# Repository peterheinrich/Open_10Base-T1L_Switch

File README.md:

# !!! UNTESTED DESIGN STUDY - WORK IN PROGRESS !!!

# Open_10Base-T1L_Switch
Open Hardware 7-Port 10Base-T1L and 1-Port 20/100/1000Base-T Field Switch Design

Schematic: [Open_10Base-T1L_Switch-sch.pdf](Open_10Base-T1L_Switch-sch.pdf)

## Architecture ##
Two 5-port switch ICs (SJA1105Q) form the basis of the design. Daisy chaining the two ICs gives a total of 8 ports.
Seven of these ports are attachted to 10Base-T1L PHYs (ADIN1100), while one port is attached to a 1000Base-T PHY (KSZ9131) as uplink. 

Each of the 10Base-T1L ports offer power over datalines utilizing two 5-Port power management controllers (LTC4296) with SCC support for power delivery negotiation. The design is 24V only and supports PoDL Class 12.

An RP2040 functions as a system controller configuring the switch components.

## Current Placement ##

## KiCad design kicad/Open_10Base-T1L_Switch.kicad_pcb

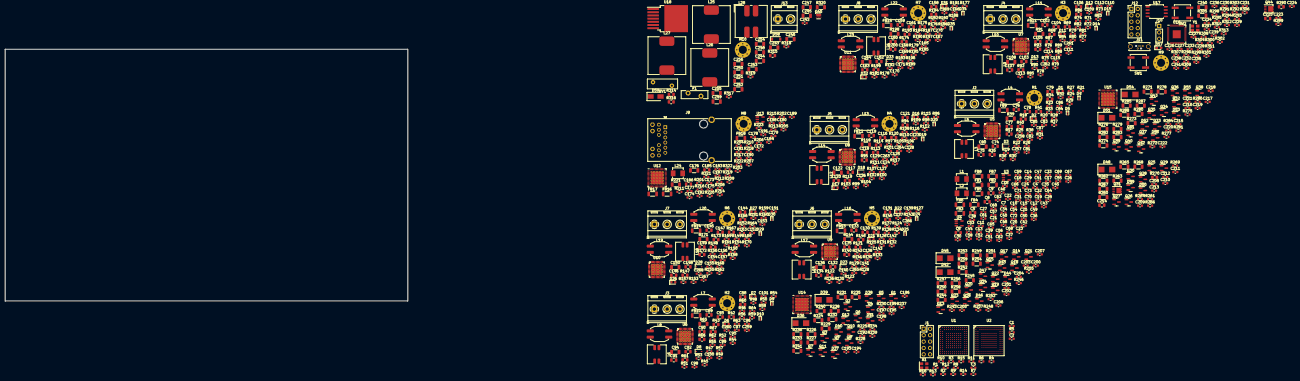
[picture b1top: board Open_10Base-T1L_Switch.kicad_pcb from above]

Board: 8 copper layers, 160.0 x 100.0 mm, 789 parts (0 on the bottom side), 588 nets, no tracks yet.

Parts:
C1, C10, C11, C12, C13, C14, C15, C16, C17, C18, C19, C20, C21, C22, C23, C24, C25, C26, C27, C29, C30, C31, C32, C33, C34, C35, C36, C37, C38, C39, C41, C42, C43, C44, C45, C46, C47, C48, C49, C50, C51, C53, C54, C55, C56, C57, C58, C59, C60, C61, C62, C63, C65, C66, C67, C68, C69, C70, C71, C72, C73, C83, C84, C85, C86, C87, C97, C98, C99, C100, C101, C111, C112, C113, C114, C115, C125, C126, C127, C128, C129, C139, C140, C141, C142, C143, C153, C154, C155, C156, C157, C167, C168, C169, C170, C171, C172, C173, C174, C175, C177, C178, C179, C180, C181, C182, C183, C184, C187, C188, C189, C190, C191, C193, C197, C201, C205, C209, C216, C220, C227, C228, C229, C230, C231, C232, C233, C234, C235, C237, C239: 100n; C_0603_1608Metric
C2, C3: 100p; C_0603_1608Metric
C4, C7, C28, C40, C52, C64, C82, C96, C110, C124, C138, C152, C166, C226, C236: 1u; C_0603_1608Metric
C5, C6, C8, C9, C185, C186: 10u; C_0805_2012Metric
C74, C75, C76, C77, C88, C89, C90, C91, C102, C103, C104, C105, C116, C117, C118, C119, C130, C131, C132, C133, C144, C145, C146, C147, C158, C159, C160, C161: 220n; C_0805_2012Metric
C78, C79, C92, C93, C106, C107, C120, C121, C134, C135, C148, C149, C162, C163: 10n; C_0805_2012Metric
C80, C94, C108, C122, C136, C150, C164, C176, C240, C256: 1u; C_1206_3216Metric
C81, C95, C109, C123, C137, C151, C165: 680n; C_0603_1608Metric
C192, C196, C200, C204, C208, C215, C219: 2u2; C_0603_1608Metric
C194, C195, C198, C199, C202, C203, C206, C207, C210, C211, C217, C218, C221, C222: 2n2; C_0603_1608Metric
C212, C213, C223, C224: 1n; C_0603_1608Metric
C214, C225: 2u2; C_0805_2012Metric
C238, C241, C258, C260, C262, C264, C266, C268, C270: 10p; C_0603_1608Metric
C242: 10n; C_0603_1608Metric
C243, C244, C245, C246, C247, C251, C252, C253, C254, C255: 22u; C_1206_3216Metric
C248, C249, C250: 47u; C_1206_3216Metric
C257, C259, C261, C263, C265, C267, C269: 8p2; C_0603_1608Metric
D1, D2, D6, D7, D11, D12, D16, D17, D21, D22, D26, D27, D31, D32: LED; LED_0603_1608Metric
D3, D8, D13, D18, D23, D28, D33: CDSOD323-T36SC; D_SOD-323
D4, D5, D9, D10, D14, D15, D19, D20, D24, D25, D29, D30, D34, D35: UCLAMP3311P; SLP1006P2
D36, D39, D42, D45, D48, D51, D54: S1B-13-F; D_SMB
D37, D40, D43, D46, D49, D52, D55: BAT54; SOT-23-DIODE
D38, D41, D44, D47, D50, D53, D56: MMBD914LT1G; SOT-23-DIODE
D57: LED; LED_0603_1608Metric_Pad1.05x0.95mm_HandSolder
D58: BZT52C10; D_SOD-123
D59: SDT5A60SA-13; D_SMA
F1: RUEF500; Fuse_Bourns_MF-RG500
FB1, FB2, FB3, FB4, FB5, FB6, FB7, FB8, FB16, FB17, FB18: 782763301; L_1206_3216Metric
FB9, FB10, FB11, FB12, FB13, FB14, FB15: FerriteBead; L_1206_3216Metric
H1, H2, H3, H4, H5, H6, H7, H8, H9, H10: CHASSIS_PE; MountingHole_3.2mm_M3_Pad_Via
J1, J12: Conn_ARM_JTAG_SWD_10; PinHeader_2x05_P2.54mm_Vertical
J2: PHY0_MDI; TerminalBlock_RND_205-00288_1x03_P5.08mm_Horizontal
J3: PHY1_MDI; TerminalBlock_RND_205-00288_1x03_P5.08mm_Horizontal
J4: PHY2_MDI; TerminalBlock_RND_205-00288_1x03_P5.08mm_Horizontal
J5: PHY3_MDI; TerminalBlock_RND_205-00288_1x03_P5.08mm_Horizontal
J6: PHY4_MDI; TerminalBlock_RND_205-00288_1x03_P5.08mm_Horizontal
J7: PHY5_MDI; TerminalBlock_RND_205-00288_1x03_P5.08mm_Horizontal
J8: PHY6_MDI; TerminalBlock_RND_205-00288_1x03_P5.08mm_Horizontal
J9: JK0654219; RJ45_Pulse_JK0654219NL_Horizontal
J10: CONSOLE; PinHeader_1x03_P2.54mm_Vertical
J11: USB_B_Micro; USB_Micro-B_Wuerth_614105150721_Vertical_CircularHoles
J13: PWR IN; TerminalBlock_RND_205-00287_1x02_P5.08mm_Horizontal
L1, L2, L24: IHLP1616BZER2R2M1A; L_Vishay_IHLP-1616
L3, L6, L9, L12, L15, L18, L21: PID75-251M
L4, L7, L10, L13, L16, L19, L22: ICI70CGI-222; ICI70CGI
L5, L8, L11, L14, L17, L20, L23: RCM70CGI-471; ICI70CGI
L25, L26, L27: MSS1583-103MED; MSS1583
L28: B82477D6103M603; L_Bourns_SRF1260
Q1, Q4, Q5, Q7, Q10, Q11, Q13, Q16, Q17, Q19, Q22, Q23, Q25, Q28, Q29, Q32, Q35, Q36, Q38, Q41, Q42: DMG3414U; SOT-23
Q2, Q8, Q14, Q20, Q26, Q33, Q39: MMBTA06; SOT-23
Q3, Q6, Q9, Q12, Q15, Q18, Q21, Q24, Q27, Q30, Q34, Q37, Q40, Q43: MMBT3904; SOT-23
Q31, Q44: SiS412DN; Vishay_PowerPAK_1212-8_Single
Q45: SiA449DJ; Vishay_PowerPAK_SC70-6L_Single
R1, R2, R3, R4, R5, R6, R7, R8, R9, R10, R11, R14, R24, R25, R27, R28, R31, R33, R36, R37, R38, R50, R51, R53, R54, R57, R59, R62, R63, R64, R76, R77, R79, R80, R83, R85, R88, R89, R90, R103, R104, R106, R107, R110, R112, R115, R116, R117, R129, R130, R132, R133, R136, R138, R141, R142, R143, R156, R157, R159, R160, R163, R165, R168, R169, R170, R183, R184, R186, R187, R190, R192, R195, R196, R197, R207, R208, R209, R210, R211, R212, R213, R214, R215, R216, R217, R218: 22; R_0603_1608Metric
R12, R15, R99, R100, R308: 1K; R_0603_1608Metric
R13, R16: 560; R_0603_1608Metric
R17, R34, R42, R60, R68, R86, R94, R113, R121, R139, R147, R166, R174, R193: 0; R_0805_2012Metric
R18, R35, R43, R61, R69, R87, R95, R114, R122, R140, R148, R167, R175, R194: 100K; R_0805_2012Metric
R19, R20, R44, R45, R70, R71, R96, R97, R123, R124, R149, R150, R176, R177, R313, R321, R322: 470; R_0603_1608Metric
R21, R46, R47, R72, R73, R125, R126, R151, R152, R153, R178, R179, R180, R317: 4K7; R_0603_1608Metric
R22, R32, R48, R58, R74, R84, R101, R111, R127, R137, R154, R164, R181, R191: 10K2; R_0603_1608Metric
R23, R30, R49, R56, R75, R82, R102, R109, R128, R135, R155, R162, R182, R189: 49.9; R_0603_1608Metric
R26, R29, R52, R55, R78, R81, R105, R108, R131, R134, R158, R161, R185, R188: 5K1; R_0603_1608Metric
R39, R65, R91, R118, R144, R171, R198, R221, R305, R320: 4M7; R_1206_3216Metric
R40, R41, R66, R67, R92, R93, R119, R120, R145, R146, R172, R173, R199, R200: 100; R_0805_2012Metric
R98, R201, R202, R203, R204, R205, R206, R219, R220, R230, R239, R248, R257, R266, R277, R286, R291, R319: 10K; R_0603_1608Metric
R222, R223, R312: 3K3; R_0603_1608Metric
R224, R233, R242, R251, R260, R271, R280: 0R24; R_1206_3216Metric
R225, R234, R243, R252, R261, R272, R281: 50K; R_0603_1608Metric
R226, R235, R244, R253, R262, R273, R282: 20; R_1206_3216Metric
R227, R236, R245, R254, R263, R274, R283: 50; R_1206_3216Metric
R228, R237, R246, R255, R264, R275, R284: 5K; R_0603_1608Metric
R229, R231, R238, R240, R247, R249, R256, R258, R265, R267, R276, R278, R285, R287: 5; R_1206_3216Metric
R232, R241, R250, R259, R268, R279, R288: 0R062; R_1206_3216Metric
R269, R289: 24K3; R_0603_1608Metric
R270, R290: 49K9; R_0805_2012Metric
R292, R296: 27; R_0603_1608Metric
R293, R294, R295, R297, R298, R299, R300, R301, R302, R303, R304, R306, R307, R309, R310, R311: 330; R_0603_1608Metric
R314, R315, R316: 1R0; R_0805_2012Metric
R318: 3K; R_0603_1608Metric
RV1: MOV-10D390K; RV_Disc_D12mm_W3.9mm_P7.5mm
SW1, SW2: USB_PGM; SW_Push_1P1T_NO_CK_KSC6xxJ
U1, U2: SJA1105Q; LFBGA_12x12mm_P0.8mm
U3, U4, U13: SC4626C; SOT-23-5
U5, U6, U7, U8, U9, U10, U11: ADIN1100; LFCSP-40_EP_TheramVias
U12: KSZ9131RNX; VQFN-48-1EP_7x7mm_P0.5mm_EP5.15x5.15mm_ThermalVias
U14, U15: LTC4296-1; QFN-48-1EP_7x7mm_P0.5mm_EP5.3x5.3mm_ThermalVias
U16: RP2040; QFN-56-1EP_7x7mm_P0.4mm_EP3.2x3.2mm
U17: IS25LP128F-JBLE; SOIC-8_5.23x5.23mm_P1.27mm
U18: LM22678TJ-ADJ; TO-263-7_TabPin8
X1: ASE-25.000MHz; Oscillator_SMD_Abracon_ASE-4Pin_3.2x2.5mm
Y1: 12MHz; Crystal_SMD_Abracon_ABM8G-4Pin_3.2x2.5mm

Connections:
25MHz_REFCLK: R14.1, U12.46 (XI)
+3V3: C1.1, C4.1, C7.1, C87.1, C101.1, C115.1, C129.1, C143.1, C157.1, C171.1, C185.1, C187.1, C188.1, C189.1, C229.1, C230.1, C231.1, C232.1, C233.1, C234.1, C235.1, C236.1, C239.1, D1.2 (A), D2.2 (A), D6.2 (A), D7.2 (A), D11.2 (A), D12.2 (A), D16.2 (A), D17.2 (A), D21.2 (A), D22.2 (A), D26.2 (A), D27.2 (A), D31.2 (A), D32.2 (A), D37.1 (K), D40.1 (K), D43.1 (K), D46.1 (K), D49.1 (K), D52.1 (K), D55.1 (K), FB1.1, FB2.1, FB3.2, FB4.2, FB9.2, FB10.2, FB11.2, FB12.2, FB13.2, FB14.2, FB15.2, FB18.2, J1.1 (VTref), J9.14 (LED2+), J9.16 (LED1+), J12.1 (VTref), L25.2, R21.2, R46.2, R47.2, R72.2, R73.2, R98.2, R99.2, R100.2, R125.2, R126.2, R151.2, R152.2, R153.2, R178.2, R179.2, R180.2, R201.1, R202.1, R203.1, R204.1, R205.1, R206.1, R222.1, R223.1, R225.2, R234.2, R243.2, R252.2, R261.2, R272.2, R281.2, R291.1, R314.1, R315.1, R316.1, R317.1, U5.35 (VDDIO), U6.35 (VDDIO), U7.35 (VDDIO), U8.35 (VDDIO), U9.35 (VDDIO), U10.35 (VDDIO), U11.35 (VDDIO), U12.16 (DVDDH), U12.34 (DVDDH), U12.40 (DVDDH), U13.1 (VIN), U16.1 (IOVDD), U16.10 (IOVDD), U16.22 (IOVDD), U16.33 (IOVDD), U16.42 (IOVDD), U16.43 (ADC_AVDD), U16.44 (VREG_IN), U16.48 (USB_VDD), U16.49 (IOVDD), U17.8 (VCC), X1.1 (EN), X1.4 (Vdd)
+24V: C212.1, C223.1, C243.1, D58.1 (K), L27.1, Q45.4 (S), R224.1, R233.1, R242.1, R251.1, R260.1, R271.1, R280.1, U14.4 (HSNSP0), U14.6 (IN), U14.36 (HSNSP4), U14.40 (HSNSP3), U14.44 (HSNSP2), U14.48 (HSNSP1), U15.4 (HSNSP0), U15.6 (IN), U15.48 (HSNSP1)
/100Base-TX-PHY7/1V2: C180.1, C181.1, C182.1, C183.1, C184.1, C186.1, FB16.2, FB17.2, L24.1, U12.18 (DVDDL), U12.23 (DVDDL), U12.26 (DVDDL), U12.30 (DVDDL), U12.39 (DVDDL), U13.4 (VOUT)
/SJA1105Q Power/1V2_A: C6.1, C10.1, C11.1, C12.1, C13.1, C14.1, C15.1, C16.1, C17.1, C26.1, C50.1, FB5.1, FB7.1, L1.1, U1.D6 (VDD_CORE), U1.D9 (VDD_CORE), U1.F4 (VDD_CORE), U1.F11 (VDD_CORE), U1.J4 (VDD_CORE), U1.J11 (VDD_CORE), U1.L6 (VDD_CORE), U1.L9 (VDD_CORE), U3.4 (VOUT)
/SJA1105Q Power/1V2_B: C9.1, C18.1, C19.1, C20.1, C21.1, C22.1, C23.1, C24.1, C25.1, C38.1, C62.1, FB6.1, FB8.1, L2.1, U2.D6 (VDD_CORE), U2.D9 (VDD_CORE), U2.F4 (VDD_CORE), U2.F11 (VDD_CORE), U2.J4 (VDD_CORE), U2.J11 (VDD_CORE), U2.L6 (VDD_CORE), U2.L9 (VDD_CORE), U4.4 (VOUT)
/System Controller/CON_USB+: J11.3 (D+), R292.1
/System Controller/CON_USB-: J11.2 (D-), R296.1
/System Controller/RP_USB+: R292.2, U16.47 (USB_DP)
/System Controller/RP_USB-: R296.2, U16.46 (USB_DM)
/System Controller/SCLK: U16.52 (QSPI_SCLK), U17.6 (CLK)
/System Controller/SD0: U16.53 (QSPI_SD0), U17.5 (DI(IO0))
/System Controller/SD1: U16.55 (QSPI_SD1), U17.2 (DO(IO1))
/System Controller/SD2: U16.54 (QSPI_SD2), U17.3 (IO2)
/System Controller/SD3: U16.51 (QSPI_SD3), U17.7 (IO3)
/System Controller/SS: R312.1, U16.56 (QSPI_SS), U17.1 (~CS)
/System Controller/UART0_RXD: J10.2, U16.3 (GPIO1)
/System Controller/UART0_TXD: J10.1, U16.2 (GPIO0)
/System Controller/nRST: C237.1, J12.10 (~RESET), R291.2, SW1.2, U16.26 (RUN)
GLOBAL_RESET: R300.2, U1.P3 (RST_N), U2.P3 (RST_N), U5.5 (RESET_N), U6.5 (RESET_N), U7.5 (RESET_N), U8.5 (RESET_N), U9.5 (RESET_N), U10.5 (RESET_N), U11.5 (RESET_N), U12.42 (RESET_N)
GND: C1.2, C4.2, C5.2, C6.2, C7.2, C8.2, C9.2, C10.2, C11.2, C12.2, C13.2, C14.2, C15.2, C16.2, C17.2, C18.2, C19.2, C20.2, C21.2, C22.2, C23.2, C24.2, C25.2, C26.2, C27.2, C28.2, C29.2, C30.2, C31.2, C32.2, C33.2, C34.2, C35.2, C36.2, C37.2, C38.2, C39.2, C40.2, C41.2, C42.2, C43.2, C44.2, C45.2, C46.2, C47.2, C48.2, C49.2, C50.2, C51.2, C52.2, C53.2, C54.2, C55.2, C56.2, C57.2, C58.2, C59.2, C60.2, C61.2, C62.2, C63.2, C64.2, C65.2, C66.2, C67.2, C68.2, C69.2, C70.2, C71.2, C72.2, C73.2, C80.2, C81.2, C82.2, C83.2, C84.2, C85.2, C86.2, C87.2, C94.2, C95.2, C96.2, C97.2, C98.2, C99.2, C100.2, C101.2, C108.2, C109.2, C110.2, C111.2, C112.2, C113.2, C114.2, C115.2, C122.2, C123.2, C124.2, C125.2, C126.2, C127.2, C128.2, C129.2, C136.2, C137.2, C138.2, C139.2, C140.2, C141.2, C142.2, C143.2, C150.2, C151.2, C152.2, C153.2, C154.2, C155.2, C156.2, C157.2, C164.2, C165.2, C166.2, C167.2, C168.2, C169.2, C170.2, C171.2, C172.1, C173.1, C174.1, C175.1, C176.2, C177.2, C178.2, C179.2, C180.2, C181.2, C182.2, C183.2, C184.2, C185.2, C186.2, C187.2, C188.2, C189.2, C190.2, C191.2, C213.1, C214.1, C224.1, C225.1, C226.2, C227.2, C228.2, C229.2, C230.2, C231.2, C232.2, C233.2, C234.2, C235.2, C236.2, C237.2, C238.2, C239.2, C240.2, C241.2, C248.2, C249.2, C250.2, C251.2, C252.2, C254.2, C255.2, C256.2, C258.2, C260.2, C262.2, C264.2, C266.2, C268.2, C270.2, D4.1 (A1), D5.1 (A1), D9.1 (A1), D10.1 (A1), D14.1 (A1), D15.1 (A1), D19.1 (A1), D20.1 (A1), D24.1 (A1), D25.1 (A1), D29.1 (A1), D30.1 (A1), D34.1 (A1), D35.1 (A1), D36.2 (A), D39.2 (A), D42.2 (A), D45.2 (A), D48.2 (A), D51.2 (A), D54.2 (A), D57.1 (K), D59.2 (A), J1.3 (GND), J1.5 (GND), J1.9 (GNDDetect), J10.3, J11.5 (GND), J12.3 (GND), J12.5 (GND), J12.9 (GNDDetect), L28.4, Q3.2 (E), Q9.2 (E), Q15.2 (E), Q21.2 (E), Q27.2 (E), Q31.1 (S), Q31.2 (S), Q31.3 (S), Q34.2 (E), Q40.2 (E), Q44.1 (S), Q44.2 (S), Q44.3 (S), R13.1, R16.1, R39.2, R40.1, R41.1, R65.2, R66.1, R67.1, R91.2, R92.1, R93.1, R118.2, R119.1, R120.1, R144.2, R145.1, R146.1, R171.2, R172.1, R173.1, R198.2, R199.1, R200.1, R219.2, R220.2, R221.2, R229.2, R238.2, R247.2, R256.2, R265.2, R269.2, R270.1, R276.2, R285.2, R289.2, R290.1, R305.2, R318.2, R319.2, R320.2, SW1.1, SW2.1, U1.A1 (VSS), U1.A14 (VSS), U1.B13 (VSS), U1.E5 (VSS), U1.E6 (VSS), U1.E7 (VSS), U1.E8 (VSS), U1.E9 (VSS), U1.E10 (VSS), U1.F5 (VSS), U1.F6 (VSS), U1.F7 (VSS), U1.F8 (VSS), U1.F9 (VSS), U1.F10 (VSS), U1.G5 (VSS), U1.G6 (VSS), U1.G7 (VSS), U1.G8 (VSS), U1.G9 (VSS), U1.G10 (VSS), U1.H5 (VSS), U1.H6 (VSS), U1.H7 (VSS), U1.H8 (VSS), U1.H9 (VSS), U1.H10 (VSS), U1.J2 (VSSA_PLL), U1.J5 (VSS), U1.J6 (VSS), U1.J7 (VSS), U1.J8 (VSS), U1.J9 (VSS), U1.J10 (VSS), U1.K4 (VSS), U1.K5 (VSS), U1.K6 (VSS), U1.K7 (VSS), U1.K8 (VSS), U1.K9 (VSS), U1.K10 (VSS), U1.L2 (VSSA_OSC), U1.L4 (i.c.), U1.L7 (VSS), U1.N2 (VSS), U1.N13 (VSS), U1.P1 (VSS), U1.P14 (VSS), U2.A1 (VSS), U2.A14 (VSS), U2.B13 (VSS), U2.E5 (VSS), U2.E6 (VSS), U2.E7 (VSS), U2.E8 (VSS), U2.E9 (VSS), U2.E10 (VSS), U2.F5 (VSS), U2.F6 (VSS), U2.F7 (VSS), U2.F8 (VSS), U2.F9 (VSS), U2.F10 (VSS), U2.G5 (VSS), U2.G6 (VSS), U2.G7 (VSS), U2.G8 (VSS), U2.G9 (VSS), U2.G10 (VSS), U2.H5 (VSS), U2.H6 (VSS), U2.H7 (VSS), U2.H8 (VSS), U2.H9 (VSS), U2.H10 (VSS), U2.J2 (VSSA_PLL), U2.J5 (VSS), U2.J6 (VSS), U2.J7 (VSS), U2.J8 (VSS), U2.J9 (VSS), U2.J10 (VSS), U2.K4 (VSS), U2.K5 (VSS), U2.K6 (VSS), U2.K7 (VSS), U2.K8 (VSS), U2.K9 (VSS), U2.K10 (VSS), U2.L2 (VSSA_OSC), U2.L4 (i.c.), U2.L7 (VSS), U2.N2 (VSS), U2.N13 (VSS), U2.P1 (VSS), U2.P14 (VSS), U3.2 (GND), U4.2 (GND), U5.41 (EP), U6.41 (EP), U7.41 (EP), U8.41 (EP), U9.41 (EP), U10.41 (EP), U11.41 (EP), U12.29 (VSS), U12.49 (EP), U13.2 (GND), U14.21 (GND), U14.24 (LSRC), U14.49 (GND), U15.21 (GND), U15.24 (LSRC), U15.49 (GND), U16.19 (TESTEN), U16.57 (GND), U17.4 (GND), U18.4 (GND), U18.8 (GND), X1.2 (GND), Y1.1, Y1.3
GNDPWR: C80.1, C94.1, C108.1, C122.1, C136.1, C150.1, C164.1, C176.1, C240.1, C256.1, H1.1, H2.1, H3.1, H4.1, H5.1, H6.1, H7.1, H8.1, H9.1, H10.1, J2.3, J3.3, J4.3, J5.3, J6.3, J7.3, J8.3, J9.SH, J11.6 (Shield), R39.1, R65.1, R91.1, R118.1, R144.1, R171.1, R198.1, R221.1, R305.1, R320.1
I2C_SCK: R222.2, R302.2, U5.27 (MDC), U6.27 (MDC), U7.27 (MDC), U8.27 (MDC), U9.27 (MDC), U10.27 (MDC), U11.27 (MDC), U12.36 (MDC)
I2C_SDA: R223.2, U5.26 (MDIO), U6.26 (MDIO), U7.26 (MDIO), U8.26 (MDIO), U9.26 (MDIO), U10.26 (MDIO), U11.26 (MDIO), U12.37 (MDIO), U16.15 (GPIO12)
MDI_PoDL_N_0: L3.2, Q6.2 (E), R227.2, R231.2, R232.2, U14.25 (OUTM0)
MDI_PoDL_N_1: L6.2, Q12.2 (E), R236.2, R240.2, R241.2, U14.27 (OUTM1)
MDI_PoDL_N_2: L9.2, Q18.2 (E), R245.2, R249.2, R250.2, U14.29 (OUTM2)
MDI_PoDL_N_3: L12.2, Q24.2 (E), R254.2, R258.2, R259.2, U14.30 (OUTM3)
MDI_PoDL_N_4: L15.2, Q30.2 (E), R263.2, R267.2, R268.2, U14.32 (OUTM4)
MDI_PoDL_N_5: L18.2, Q37.2 (E), R274.2, R278.2, R279.2, U15.25 (OUTM0)
MDI_PoDL_N_6: L21.2, Q43.2 (E), R283.2, R287.2, R288.2, U15.27 (OUTM1)
MDI_PoDL_P_0: C192.1, C193.1, C194.1, D36.1 (K), L3.3, Q1.3 (D), Q2.3 (C), Q4.2 (S), U14.1 (OUTP0)
MDI_PoDL_P_1: C196.1, C197.1, C198.1, D39.1 (K), L6.3, Q7.3 (D), Q8.3 (C), Q10.2 (S), U14.45 (OUTP1)
MDI_PoDL_P_2: C200.1, C201.1, C202.1, D42.1 (K), L9.3, Q13.3 (D), Q14.3 (C), Q16.2 (S), U14.41 (OUTP2)
MDI_PoDL_P_3: C204.1, C205.1, C206.1, D45.1 (K), L12.3, Q19.3 (D), Q20.3 (C), Q22.2 (S), U14.37 (OUTP3)
MDI_PoDL_P_4: C208.1, C209.1, C210.1, D48.1 (K), L15.3, Q25.3 (D), Q26.3 (C), Q28.2 (S), U14.33 (OUTP4)
MDI_PoDL_P_5: C215.1, C216.1, C217.1, D51.1 (K), L18.3, Q32.3 (D), Q33.3 (C), Q35.2 (S), U15.1 (OUTP0)
MDI_PoDL_P_6: C219.1, C220.1, C221.1, D54.1 (K), L21.3, Q38.3 (D), Q39.3 (C), Q41.2 (S), U15.45 (OUTP1)
MDI_SSCPI_0: Q2.2 (E), U16.13 (GPIO10)
MDI_SSCPI_1: Q8.2 (E), U16.17 (GPIO14)
MDI_SSCPI_2: Q14.2 (E), U16.27 (GPIO16)
MDI_SSCPI_3: Q20.2 (E), U16.29 (GPIO18)
MDI_SSCPI_4: Q26.2 (E), U16.31 (GPIO20)
MDI_SSCPI_5: Q33.2 (E), U16.34 (GPIO22)
MDI_SSCPI_6: Q39.2 (E), U16.36 (GPIO24)
MDI_SSCPO_0: R228.1, R301.2
MDI_SSCPO_1: R237.1, R303.2
MDI_SSCPO_2: R246.1, R304.2
MDI_SSCPO_3: R255.1, R306.2
MDI_SSCPO_4: R264.1, R307.2
MDI_SSCPO_5: R275.1, R309.2
MDI_SSCPO_6: R284.1, R310.2
unnamed: C2.1, R12.2, R13.2
unnamed: C2.2, U1.K2 (OSC_IN)
unnamed: C3.1, R15.2, R16.2
unnamed: C3.2, U2.K2 (OSC_IN)
unnamed: C5.1, FB1.2, U3.1 (VIN)
unnamed: C8.1, FB2.2, U4.1 (VIN)
unnamed: C27.1, C28.1, FB5.2, U1.J1 (VDDA_PLL)
unnamed: C29.1, C30.1, C31.1, C32.1, C33.1, C34.1, C35.1, C36.1, C37.1, C53.1, C54.1, C55.1, C56.1, C57.1, C58.1, C59.1, C60.1, C61.1, FB3.1, U1.D4 (VDDIO_MII0), U1.D5 (VDDIO_MII1), U1.D7 (VDDIO_MII1), U1.D8 (VDDIO_MII1), U1.D10 (VDDIO_MII2), U1.D11 (VDDIO_MII2), U1.E4 (VDDIO_MII0), U1.E11 (VDDIO_MII2), U1.G4 (VDDIO_MII0), U1.G11 (VDDIO_MII3), U1.H4 (VDDIO_CLO), U1.H11 (VDDIO_MII3), U1.K11 (VDDIO_MII3), U1.L5 (VDDIO_HOST), U1.L8 (VDDIO_MII4), U1.L10 (VDDIO_MII4), U1.L11 (VDDIO_MII4)
unnamed: C39.1, C40.1, FB6.2, U2.J1 (VDDA_PLL)
unnamed: C41.1, C42.1, C43.1, C44.1, C45.1, C46.1, C47.1, C48.1, C49.1, C65.1, C66.1, C67.1, C68.1, C69.1, C70.1, C71.1, C72.1, C73.1, FB4.1, U2.D4 (VDDIO_MII0), U2.D5 (VDDIO_MII1), U2.D7 (VDDIO_MII1), U2.D8 (VDDIO_MII1), U2.D10 (VDDIO_MII2), U2.D11 (VDDIO_MII2), U2.E4 (VDDIO_MII0), U2.E11 (VDDIO_MII2), U2.G4 (VDDIO_MII0), U2.G11 (VDDIO_MII3), U2.H4 (VDDIO_CLO), U2.H11 (VDDIO_MII3), U2.K11 (VDDIO_MII3), U2.L5 (VDDIO_HOST), U2.L8 (VDDIO_MII4), U2.L10 (VDDIO_MII4), U2.L11 (VDDIO_MII4)
unnamed: C51.1, C52.1, FB7.2, U1.K1 (VDDA_OSC)
unnamed: C63.1, C64.1, FB8.2, U2.K1 (VDDA_OSC)
unnamed: C74.1, D5.2 (A2), R17.1, R23.2, R26.2
unnamed: C74.2, L4.2, R17.2
unnamed: C75.1, L4.1, R18.1
unnamed: C75.2, L5.1, R18.2
unnamed: C76.1, D4.2 (A2), R29.2, R30.2, R34.1
unnamed: C76.2, L4.3, R34.2
unnamed: C77.1, L4.4, R35.1
unnamed: C77.2, L5.2, R35.2
unnamed: C78.1, D3.1 (A1), J2.2, L3.1, L5.4
unnamed: C78.2, R40.2
unnamed: C79.1, D3.2 (A2), J2.1, L3.4, L5.3
unnamed: C79.2, R41.2
unnamed: C81.1, U5.23 (DLDO_1P1), U5.24 (DVDD_1P1)
unnamed: C82.1, U5.20 (CEXT_3)
unnamed: C83.1, U5.19 (CEXT_2)
unnamed: C84.1, C85.1, C86.1, FB9.1, U5.16 (AVDD_H), U5.17 (AVDD_H), U5.22 (AVDD_L)
unnamed: C88.1, D10.2 (A2), R42.1, R49.2, R52.2
unnamed: C88.2, L7.2, R42.2
unnamed: C89.1, L7.1, R43.1
unnamed: C89.2, L8.1, R43.2
unnamed: C90.1, D9.2 (A2), R55.2, R56.2, R60.1
unnamed: C90.2, L7.3, R60.2
unnamed: C91.1, L7.4, R61.1
unnamed: C91.2, L8.2, R61.2
unnamed: C92.1, D8.1 (A1), J3.2, L6.1, L8.4
unnamed: C92.2, R66.2
unnamed: C93.1, D8.2 (A2), J3.1, L6.4, L8.3
unnamed: C93.2, R67.2
unnamed: C95.1, U6.23 (DLDO_1P1), U6.24 (DVDD_1P1)
unnamed: C96.1, U6.20 (CEXT_3)
unnamed: C97.1, U6.19 (CEXT_2)
unnamed: C98.1, C99.1, C100.1, FB10.1, U6.16 (AVDD_H), U6.17 (AVDD_H), U6.22 (AVDD_L)
unnamed: C102.1, D15.2 (A2), R68.1, R75.2, R78.2
unnamed: C102.2, L10.2, R68.2
unnamed: C103.1, L10.1, R69.1
unnamed: C103.2, L11.1, R69.2
unnamed: C104.1, D14.2 (A2), R81.2, R82.2, R86.1
unnamed: C104.2, L10.3, R86.2
unnamed: C105.1, L10.4, R87.1
unnamed: C105.2, L11.2, R87.2
unnamed: C106.1, D13.1 (A1), J4.2, L9.1, L11.4
unnamed: C106.2, R92.2
unnamed: C107.1, D13.2 (A2), J4.1, L9.4, L11.3
unnamed: C107.2, R93.2
unnamed: C109.1, U7.23 (DLDO_1P1), U7.24 (DVDD_1P1)
unnamed: C110.1, U7.20 (CEXT_3)
unnamed: C111.1, U7.19 (CEXT_2)
unnamed: C112.1, C113.1, C114.1, FB11.1, U7.16 (AVDD_H), U7.17 (AVDD_H), U7.22 (AVDD_L)
unnamed: C116.1, D20.2 (A2), R94.1, R102.2, R105.2
unnamed: C116.2, L13.2, R94.2
unnamed: C117.1, L13.1, R95.1
unnamed: C117.2, L14.1, R95.2
unnamed: C118.1, D19.2 (A2), R108.2, R109.2, R113.1
unnamed: C118.2, L13.3, R113.2
unnamed: C119.1, L13.4, R114.1
unnamed: C119.2, L14.2, R114.2
unnamed: C120.1, D18.1 (A1), J5.2, L12.1, L14.4
unnamed: C120.2, R119.2
unnamed: C121.1, D18.2 (A2), J5.1, L12.4, L14.3
unnamed: C121.2, R120.2
unnamed: C123.1, U8.23 (DLDO_1P1), U8.24 (DVDD_1P1)
unnamed: C124.1, U8.20 (CEXT_3)
unnamed: C125.1, U8.19 (CEXT_2)
unnamed: C126.1, C127.1, C128.1, FB12.1, U8.16 (AVDD_H), U8.17 (AVDD_H), U8.22 (AVDD_L)
unnamed: C130.1, D25.2 (A2), R121.1, R128.2, R131.2
unnamed: C130.2, L16.2, R121.2
unnamed: C131.1, L16.1, R122.1
unnamed: C131.2, L17.1, R122.2
unnamed: C132.1, D24.2 (A2), R134.2, R135.2, R139.1
unnamed: C132.2, L16.3, R139.2
unnamed: C133.1, L16.4, R140.1
unnamed: C133.2, L17.2, R140.2
unnamed: C134.1, D23.1 (A1), J6.2, L15.1, L17.4
unnamed: C134.2, R145.2
unnamed: C135.1, D23.2 (A2), J6.1, L15.4, L17.3
unnamed: C135.2, R146.2
unnamed: C137.1, U9.23 (DLDO_1P1), U9.24 (DVDD_1P1)
unnamed: C138.1, U9.20 (CEXT_3)
unnamed: C139.1, U9.19 (CEXT_2)
unnamed: C140.1, C141.1, C142.1, FB13.1, U9.16 (AVDD_H), U9.17 (AVDD_H), U9.22 (AVDD_L)
unnamed: C144.1, D30.2 (A2), R147.1, R155.2, R158.2
unnamed: C144.2, L19.2, R147.2
unnamed: C145.1, L19.1, R148.1
unnamed: C145.2, L20.1, R148.2
unnamed: C146.1, D29.2 (A2), R161.2, R162.2, R166.1
unnamed: C146.2, L19.3, R166.2
unnamed: C147.1, L19.4, R167.1
unnamed: C147.2, L20.2, R167.2
unnamed: C148.1, D28.1 (A1), J7.2, L18.1, L20.4
unnamed: C148.2, R172.2
unnamed: C149.1, D28.2 (A2), J7.1, L18.4, L20.3
unnamed: C149.2, R173.2
unnamed: C151.1, U10.23 (DLDO_1P1), U10.24 (DVDD_1P1)
unnamed: C152.1, U10.20 (CEXT_3)
unnamed: C153.1, U10.19 (CEXT_2)
unnamed: C154.1, C155.1, C156.1, FB14.1, U10.16 (AVDD_H), U10.17 (AVDD_H), U10.22 (AVDD_L)
unnamed: C158.1, D35.2 (A2), R174.1, R182.2, R185.2
unnamed: C158.2, L22.2, R174.2
unnamed: C159.1, L22.1, R175.1
unnamed: C159.2, L23.1, R175.2
unnamed: C160.1, D34.2 (A2), R188.2, R189.2, R193.1
unnamed: C160.2, L22.3, R193.2
unnamed: C161.1, L22.4, R194.1
unnamed: C161.2, L23.2, R194.2
unnamed: C162.1, D33.1 (A1), J8.2, L21.1, L23.4
unnamed: C162.2, R199.2
unnamed: C163.1, D33.2 (A2), J8.1, L21.4, L23.3
unnamed: C163.2, R200.2
unnamed: C165.1, U11.23 (DLDO_1P1), U11.24 (DVDD_1P1)
unnamed: C166.1, U11.20 (CEXT_3)
unnamed: C167.1, U11.19 (CEXT_2)
unnamed: C168.1, C169.1, C170.1, FB15.1, U11.16 (AVDD_H), U11.17 (AVDD_H), U11.22 (AVDD_L)
unnamed: C172.2, J9.12 (MXCT1)
unnamed: C173.2, J9.6 (MXCT2)
unnamed: C174.2, J9.1 (MXCT3)
unnamed: C175.2, J9.7 (MXCT4)
unnamed: C177.1, C178.1, FB16.1, U12.4 (AVDDL), U12.9 (AVDDL)
unnamed: C179.1, FB17.1, U12.44 (AVDDL_PLL)
unnamed: C190.1, C191.1, FB18.1, U12.1 (AVDDH), U12.12 (AVDDH)
unnamed: C192.2, R226.1
unnamed: C193.2, R227.1
unnamed: C194.2, Q1.1 (G), Q3.3 (C), R228.2
unnamed: C195.1, D38.1 (K), Q5.3 (D), R226.2
unnamed: C195.2, Q5.1 (G), Q6.3 (C), R230.2
unnamed: C196.2, R235.1
unnamed: C197.2, R236.1
unnamed: C198.2, Q7.1 (G), Q9.3 (C), R237.2
unnamed: C199.1, D41.1 (K), Q11.3 (D), R235.2
unnamed: C199.2, Q11.1 (G), Q12.3 (C), R239.2
unnamed: C200.2, R244.1
unnamed: C201.2, R245.1
unnamed: C202.2, Q13.1 (G), Q15.3 (C), R246.2
unnamed: C203.1, D44.1 (K), Q17.3 (D), R244.2
unnamed: C203.2, Q17.1 (G), Q18.3 (C), R248.2
unnamed: C204.2, R253.1
unnamed: C205.2, R254.1
unnamed: C206.2, Q19.1 (G), Q21.3 (C), R255.2
unnamed: C207.1, D47.1 (K), Q23.3 (D), R253.2
unnamed: C207.2, Q23.1 (G), Q24.3 (C), R257.2
unnamed: C208.2, R262.1
unnamed: C209.2, R263.1
unnamed: C210.2, Q25.1 (G), Q27.3 (C), R264.2
unnamed: C211.1, D50.1 (K), Q29.3 (D), R262.2
unnamed: C211.2, Q29.1 (G), Q30.3 (C), R266.2
unnamed: C212.2, U14.7 (CPO)
unnamed: C213.2, U14.8 (INT)
unnamed: C215.2, R273.1
unnamed: C216.2, R274.1
unnamed: C217.2, Q32.1 (G), Q34.3 (C), R275.2
unnamed: C218.1, D53.1 (K), Q36.3 (D), R273.2
unnamed: C218.2, Q36.1 (G), Q37.3 (C), R277.2
unnamed: C219.2, R282.1
unnamed: C220.2, R283.1
unnamed: C221.2, Q38.1 (G), Q40.3 (C), R284.2
unnamed: C222.1, D56.1 (K), Q42.3 (D), R282.2
unnamed: C222.2, Q42.1 (G), Q43.3 (C), R286.2
unnamed: C223.2, U15.7 (CPO)
unnamed: C224.2, U15.8 (INT)
unnamed: C226.1, C227.1, C228.1, U16.23 (DVDD), U16.45 (VREG_VOUT), U16.50 (DVDD)
unnamed: C238.1, U16.20 (XIN), Y1.2
unnamed: C241.1, R308.1, Y1.4
unnamed: C242.1, U18.3 (BOOT)
unnamed: C242.2, D59.1 (K), L25.1, U18.1 (SW)
unnamed: C243.2, C251.1
unnamed: C244.1, L27.2, U18.2 (VIN)
unnamed: C244.2, C252.1
unnamed: C245.1, F1.2, L28.1, RV1.1
unnamed: C245.2, C253.1
unnamed: C246.1, L26.1, L28.3
unnamed: C246.2, C254.1
unnamed: C247.1, L26.2, Q45.1 (D)
unnamed: C247.2, C255.1
unnamed: C248.1, R314.2
unnamed: C249.1, R315.2
unnamed: C250.1, R316.2
unnamed: C253.2, J13.2, L28.2, RV1.2
unnamed: C257.1, R31.2
unnamed: C257.2, C258.1, U5.8 (XTAL_I/CLK_IN)
unnamed: C259.1, R57.2
unnamed: C259.2, C260.1, U6.8 (XTAL_I/CLK_IN)
unnamed: C261.1, R83.2
unnamed: C261.2, C262.1, U7.8 (XTAL_I/CLK_IN)
unnamed: C263.1, R110.2
unnamed: C263.2, C264.1, U8.8 (XTAL_I/CLK_IN)
unnamed: C265.1, R136.2
unnamed: C265.2, C266.1, U9.8 (XTAL_I/CLK_IN)
unnamed: C267.1, R163.2
unnamed: C267.2, C268.1, U10.8 (XTAL_I/CLK_IN)
unnamed: C269.1, R190.2
unnamed: C269.2, C270.1, U11.8 (XTAL_I/CLK_IN)
unnamed: D1.1 (K), R19.2
unnamed: D2.1 (K), R20.2
unnamed: D6.1 (K), R44.2
unnamed: D7.1 (K), R45.2
unnamed: D11.1 (K), R70.2
unnamed: D12.1 (K), R71.2
unnamed: D16.1 (K), R96.2
unnamed: D17.1 (K), R97.2
unnamed: D21.1 (K), R123.2
unnamed: D22.1 (K), R124.2
unnamed: D26.1 (K), R149.2
unnamed: D27.1 (K), R150.2
unnamed: D31.1 (K), R176.2
unnamed: D32.1 (K), R177.2
unnamed: D37.2 (A), Q2.1 (B), R225.1
unnamed: D38.2 (A), Q5.2 (S), Q6.1 (B), R231.1
unnamed: D40.2 (A), Q8.1 (B), R234.1
unnamed: D41.2 (A), Q11.2 (S), Q12.1 (B), R240.1
unnamed: D43.2 (A), Q14.1 (B), R243.1
unnamed: D44.2 (A), Q17.2 (S), Q18.1 (B), R249.1
unnamed: D46.2 (A), Q20.1 (B), R252.1
unnamed: D47.2 (A), Q23.2 (S), Q24.1 (B), R258.1
unnamed: D49.2 (A), Q26.1 (B), R261.1
unnamed: D50.2 (A), Q29.2 (S), Q30.1 (B), R267.1
unnamed: D52.2 (A), Q33.1 (B), R272.1
unnamed: D53.2 (A), Q36.2 (S), Q37.1 (B), R278.1
unnamed: D55.2 (A), Q39.1 (B), R281.1
unnamed: D56.2 (A), Q42.2 (S), Q43.1 (B), R287.1
unnamed: D57.2 (A), R313.2
unnamed: D58.2 (A), Q45.3 (G), R319.1
unnamed: F1.1, J13.1
unnamed: J1.2 (SWDIO/TMS), U1.P2 (TMS), U2.P2 (TMS)
unnamed: J1.4 (SWDCLK/TCK), U1.N1 (TCK), U2.N1 (TCK)
unnamed: J1.6 (SWO/TDO), U1.M2 (TDI)
unnamed: J1.8 (NC/TDI), U2.N3 (TDO)
unnamed: J1.10 (~RESET), U1.M1 (TRST_N), U2.M1 (TRST_N)
unnamed: J9.2 (MX3-), U12.8 (TXRXM_C)
unnamed: J9.3 (MX3+), U12.7 (TXRXP_C)
unnamed: J9.4 (MX2+), U12.5 (TXRXP_B)
unnamed: J9.5 (MX2-), U12.6 (TXRXM_B)
unnamed: J9.8 (MX4+), U12.10 (TXRXP_D)
unnamed: J9.9 (MX4-), U12.11 (TXRXM_D)
unnamed: J9.10 (MX1-), U12.3 (TXRXM_A)
unnamed: J9.11 (MX1+), U12.2 (TXRXP_A)
unnamed: J9.13 (LED2-), R322.2
unnamed: J9.15 (LED1-), R321.2
unnamed: J12.2 (SWDIO/TMS), U16.25 (SWD)
unnamed: J12.4 (SWDCLK/TCK), U16.24 (SWCLK)
unnamed: L1.2, U3.5 (LX)
unnamed: L2.2, U4.5 (LX)
unnamed: L24.2, U13.5 (LX)
unnamed: Q1.2 (S), Q3.1 (B), R229.1
unnamed: Q4.1 (G), U14.2 (HGATE0)
unnamed: Q4.3 (D), R224.2, U14.3 (HSNSM0)
unnamed: Q7.2 (S), Q9.1 (B), R238.1
unnamed: Q10.1 (G), U14.46 (HGATE1)
unnamed: Q10.3 (D), R233.2, U14.47 (HSNSM1)
unnamed: Q13.2 (S), Q15.1 (B), R247.1
unnamed: Q16.1 (G), U14.42 (HGATE2)
unnamed: Q16.3 (D), R242.2, U14.43 (HSNSM2)
unnamed: Q19.2 (S), Q21.1 (B), R256.1
unnamed: Q22.1 (G), U14.38 (HGATE3)
unnamed: Q22.3 (D), R251.2, U14.39 (HSNSM3)
unnamed: Q25.2 (S), Q27.1 (B), R265.1
unnamed: Q28.1 (G), U14.34 (HGATE4)
unnamed: Q28.3 (D), R260.2, U14.35 (HSNSM4)
unnamed: Q31.4 (G), U14.23 (LGATE)
unnamed: Q32.2 (S), Q34.1 (B), R276.1
unnamed: Q35.1 (G), U15.2 (HGATE0)
unnamed: Q35.3 (D), R271.2, U15.3 (HSNSM0)
unnamed: Q38.2 (S), Q40.1 (B), R285.1
unnamed: Q41.1 (G), U15.46 (HGATE1)
unnamed: Q41.3 (D), R280.2, U15.47 (HSNSM1)
unnamed: Q44.4 (G), U15.23 (LGATE)
unnamed: R1.1, U1.N9 (MII4_TX_CLK)
unnamed: R1.2, U2.D1 (MII0_TX_CLK)
unnamed: R2.1, U1.P9 (MII4_TX_EN)
unnamed: R2.2, U2.G1 (MII0_RX_DV)
unnamed: R3.1, U1.N12 (MII4_RX_DV)
unnamed: R3.2, U2.D2 (MII0_TX_EN)
unnamed: R4.1, U1.P6 (MII4_TX_ER)
unnamed: R4.2, U2.H2 (MII0_RX_ER)
unnamed: R5.1, U1.P13 (MII4_RX_ER)
unnamed: R5.2, U2.A3 (MII0_TX_ER)
unnamed: R6.1, U1.P7 (MII4_TXD0)
unnamed: R6.2, U2.E1 (MII0_RXD0)
unnamed: R7.1, U1.N10 (MII4_RXD0)
unnamed: R7.2, U2.A2 (MII0_TXD0)
unnamed: R8.1, U1.N7 (MII4_TXD1)
unnamed: R8.2, U2.F2 (MII0_RXD1)
unnamed: R9.1, U1.P11 (MII4_RXD1)
unnamed: R9.2, U2.B1 (MII0_TXD1)
unnamed: R10.1, R15.1
unnamed: R10.2, U1.H1 (CLK_OUT)
unnamed: R11.1, X1.3 (OUT)
unnamed: R11.2, R12.1
unnamed: R14.2, U2.H1 (CLK_OUT)
unnamed: R19.1, U5.3 (LED_0)
unnamed: R20.1, U5.6 (LED_1)
unnamed: R21.1, R24.1, U1.G1 (MII0_RX_DV)
unnamed: R22.1, R23.1, U5.12 (TXN)
unnamed: R22.2, R29.1, U5.14 (RXP)
unnamed: R24.2, U5.33 (RX_DV/SWPD_ENB)
unnamed: R25.1, U1.H2 (MII0_RX_ER)
unnamed: R25.2, U5.34 (RX_ER/MACIF_SEL1)
unnamed: R26.1, R32.2, U5.13 (RXN)
unnamed: R27.1, U1.E1 (MII0_RXD0)
unnamed: R27.2, U5.31 (RXD_0/TX2P4_ENB)
unnamed: R28.1, U1.F2 (MII0_RXD1)
unnamed: R28.2, U5.30 (RXD_1/MS_SEL2)
unnamed: R30.1, R32.1, U5.15 (TXP)
unnamed: R31.1, U1.D1 (MII0_TX_CLK)
unnamed: R33.1, U1.D2 (MII0_TX_EN)
unnamed: R33.2, U5.37 (TX_EN)
unnamed: R36.1, U1.A3 (MII0_TX_ER)
unnamed: R36.2, U5.36 (TX_ER)
unnamed: R37.1, U1.A2 (MII0_TXD0)
unnamed: R37.2, U5.39 (TXD_0)
unnamed: R38.1, U1.B1 (MII0_TXD1)
unnamed: R38.2, U5.40 (TXD_1)
unnamed: R44.1, U6.3 (LED_0)
unnamed: R45.1, U6.6 (LED_1)
unnamed: R46.1, R50.1, U1.A4 (MII1_RX_DV)
unnamed: R47.1, U6.29 (RXD_2/PHYAD_0)
unnamed: R48.1, R49.1, U6.12 (TXN)
unnamed: R48.2, R55.1, U6.14 (RXP)
unnamed: R50.2, U6.33 (RX_DV/SWPD_ENB)
unnamed: R51.1, U1.B3 (MII1_RX_ER)
unnamed: R51.2, U6.34 (RX_ER/MACIF_SEL1)
unnamed: R52.1, R58.2, U6.13 (RXN)
unnamed: R53.1, U1.A6 (MII1_RXD0)
unnamed: R53.2, U6.31 (RXD_0/TX2P4_ENB)
unnamed: R54.1, U1.B5 (MII1_RXD1)
unnamed: R54.2, U6.30 (RXD_1/MS_SEL2)
unnamed: R56.1, R58.1, U6.15 (TXP)
unnamed: R57.1, U1.A7 (MII1_TX_CLK)
unnamed: R59.1, U1.B7 (MII1_TX_EN)
unnamed: R59.2, U6.37 (TX_EN)
unnamed: R62.1, U1.A10 (MII1_TX_ER)
unnamed: R62.2, U6.36 (TX_ER)
unnamed: R63.1, U1.B9 (MII1_TXD0)
unnamed: R63.2, U6.39 (TXD_0)
unnamed: R64.1, U1.A9 (MII1_TXD1)
unnamed: R64.2, U6.40 (TXD_1)
unnamed: R70.1, U7.3 (LED_0)
unnamed: R71.1, U7.6 (LED_1)
unnamed: R72.1, R76.1, U1.A11 (MII2_RX_DV)
unnamed: R73.1, U7.28 (RXD_3/PHYAD_1)
unnamed: R74.1, R75.1, U7.12 (TXN)
unnamed: R74.2, R81.1, U7.14 (RXP)
unnamed: R76.2, U7.33 (RX_DV/SWPD_ENB)
unnamed: R77.1, U1.B10 (MII2_RX_ER)
unnamed: R77.2, U7.34 (RX_ER/MACIF_SEL1)
unnamed: R78.1, R84.2, U7.13 (RXN)
unnamed: R79.1, U1.A13 (MII2_RXD0)
unnamed: R79.2, U7.31 (RXD_0/TX2P4_ENB)
unnamed: R80.1, U1.B12 (MII2_RXD1)
unnamed: R80.2, U7.30 (RXD_1/MS_SEL2)
unnamed: R82.1, R84.1, U7.15 (TXP)
unnamed: R83.1, U1.C14 (MII2_TX_CLK)
unnamed: R85.1, U1.C13 (MII2_TX_EN)
unnamed: R85.2, U7.37 (TX_EN)
unnamed: R88.1, U1.F14 (MII2_TX_ER)
unnamed: R88.2, U7.36 (TX_ER)
unnamed: R89.1, U1.E13 (MII2_TXD0)
unnamed: R89.2, U7.39 (TXD_0)
unnamed: R90.1, U1.E14 (MII2_TXD1)
unnamed: R90.2, U7.40 (TXD_1)
unnamed: R96.1, U8.3 (LED_0)
unnamed: R97.1, U8.6 (LED_1)
unnamed: R99.1, U8.28 (RXD_3/PHYAD_1)
unnamed: R100.1, U8.29 (RXD_2/PHYAD_0)
unnamed: R101.1, R102.1, U8.12 (TXN)
unnamed: R101.2, R108.1, U8.14 (RXP)
unnamed: R98.1, R103.1, U1.G14 (MII3_RX_DV)
unnamed: R103.2, U8.33 (RX_DV/SWPD_ENB)
unnamed: R104.1, U1.F13 (MII3_RX_ER)
unnamed: R104.2, U8.34 (RX_ER/MACIF_SEL1)
unnamed: R105.1, R111.2, U8.13 (RXN)
unnamed: R106.1, U1.J14 (MII3_RXD0)
unnamed: R106.2, U8.31 (RXD_0/TX2P4_ENB)
unnamed: R107.1, U1.H13 (MII3_RXD1)
unnamed: R107.2, U8.30 (RXD_1/MS_SEL2)
unnamed: R109.1, R111.1, U8.15 (TXP)
unnamed: R110.1, U1.K14 (MII3_TX_CLK)
unnamed: R112.1, U1.K13 (MII3_TX_EN)
unnamed: R112.2, U8.37 (TX_EN)
unnamed: R115.1, U1.N14 (MII3_TX_ER)
unnamed: R115.2, U8.36 (TX_ER)
unnamed: R116.1, U1.M13 (MII3_TXD0)
unnamed: R116.2, U8.39 (TXD_0)
unnamed: R117.1, U1.M14 (MII3_TXD1)
unnamed: R117.2, U8.40 (TXD_1)
unnamed: R123.1, U9.3 (LED_0)
unnamed: R124.1, U9.6 (LED_1)
unnamed: R125.1, R129.1, U2.A4 (MII1_RX_DV)
unnamed: R126.1, U9.4 (LINK_ST/PHYAD_2)
unnamed: R127.1, R128.1, U9.12 (TXN)
unnamed: R127.2, R134.1, U9.14 (RXP)
unnamed: R129.2, U9.33 (RX_DV/SWPD_ENB)
unnamed: R130.1, U2.B3 (MII1_RX_ER)
unnamed: R130.2, U9.34 (RX_ER/MACIF_SEL1)
unnamed: R131.1, R137.2, U9.13 (RXN)
unnamed: R132.1, U2.A6 (MII1_RXD0)
unnamed: R132.2, U9.31 (RXD_0/TX2P4_ENB)
unnamed: R133.1, U2.B5 (MII1_RXD1)
unnamed: R133.2, U9.30 (RXD_1/MS_SEL2)
unnamed: R135.1, R137.1, U9.15 (TXP)
unnamed: R136.1, U2.A7 (MII1_TX_CLK)
unnamed: R138.1, U2.B7 (MII1_TX_EN)
unnamed: R138.2, U9.37 (TX_EN)
unnamed: R141.1, U2.A10 (MII1_TX_ER)
unnamed: R141.2, U9.36 (TX_ER)
unnamed: R142.1, U2.B9 (MII1_TXD0)
unnamed: R142.2, U9.39 (TXD_0)
unnamed: R143.1, U2.A9 (MII1_TXD1)
unnamed: R143.2, U9.40 (TXD_1)
unnamed: R149.1, U10.3 (LED_0)
unnamed: R150.1, U10.6 (LED_1)
unnamed: R151.1, R156.1, U2.A11 (MII2_RX_DV)
unnamed: R152.1, U10.4 (LINK_ST/PHYAD_2)
unnamed: R153.1, U10.29 (RXD_2/PHYAD_0)
unnamed: R154.1, R155.1, U10.12 (TXN)
unnamed: R154.2, R161.1, U10.14 (RXP)
unnamed: R156.2, U10.33 (RX_DV/SWPD_ENB)
unnamed: R157.1, U2.B10 (MII2_RX_ER)
unnamed: R157.2, U10.34 (RX_ER/MACIF_SEL1)
unnamed: R158.1, R164.2, U10.13 (RXN)
unnamed: R159.1, U2.A13 (MII2_RXD0)
unnamed: R159.2, U10.31 (RXD_0/TX2P4_ENB)
unnamed: R160.1, U2.B12 (MII2_RXD1)
unnamed: R160.2, U10.30 (RXD_1/MS_SEL2)
unnamed: R162.1, R164.1, U10.15 (TXP)
unnamed: R163.1, U2.C14 (MII2_TX_CLK)
unnamed: R165.1, U2.C13 (MII2_TX_EN)
unnamed: R165.2, U10.37 (TX_EN)
unnamed: R168.1, U2.F14 (MII2_TX_ER)
unnamed: R168.2, U10.36 (TX_ER)
unnamed: R169.1, U2.E13 (MII2_TXD0)
unnamed: R169.2, U10.39 (TXD_0)
unnamed: R170.1, U2.E14 (MII2_TXD1)
unnamed: R170.2, U10.40 (TXD_1)
unnamed: R176.1, U11.3 (LED_0)
unnamed: R177.1, U11.6 (LED_1)
unnamed: R178.1, R183.1, U2.G14 (MII3_RX_DV)
unnamed: R179.1, U11.4 (LINK_ST/PHYAD_2)
unnamed: R180.1, U11.28 (RXD_3/PHYAD_1)
unnamed: R181.1, R182.1, U11.12 (TXN)
unnamed: R181.2, R188.1, U11.14 (RXP)
unnamed: R183.2, U11.33 (RX_DV/SWPD_ENB)
unnamed: R184.1, U2.F13 (MII3_RX_ER)
unnamed: R184.2, U11.34 (RX_ER/MACIF_SEL1)
unnamed: R185.1, R191.2, U11.13 (RXN)
unnamed: R186.1, U2.J14 (MII3_RXD0)
unnamed: R186.2, U11.31 (RXD_0/TX2P4_ENB)
unnamed: R187.1, U2.H13 (MII3_RXD1)
unnamed: R187.2, U11.30 (RXD_1/MS_SEL2)
unnamed: R189.1, R191.1, U11.15 (TXP)
unnamed: R190.1, U2.K14 (MII3_TX_CLK)
unnamed: R192.1, U2.K13 (MII3_TX_EN)
unnamed: R192.2, U11.37 (TX_EN)
unnamed: R195.1, U2.N14 (MII3_TX_ER)
unnamed: R195.2, U11.36 (TX_ER)
unnamed: R196.1, U2.M13 (MII3_TXD0)
unnamed: R196.2, U11.39 (TXD_0)
unnamed: R197.1, U2.M14 (MII3_TXD1)
unnamed: R197.2, U11.40 (TXD_1)
unnamed: R201.2, R212.1, U2.P12 (MII4_RXD3)
unnamed: R202.2, R211.1, U2.N11 (MII4_RXD2)
unnamed: R203.2, R210.1, U2.P11 (MII4_RXD1)
unnamed: R204.2, R207.1, U2.P10 (MII4_RX_CLK)
unnamed: R205.2, R321.1, U12.17 (LED1/PME_N1/PHYAD0)
unnamed: R206.2, R322.1, U12.15 (LED2/PHYAD1)
unnamed: R207.2, U12.35 (RXC/PHYAD2)
unnamed: R208.1, R220.1, U2.N12 (MII4_RX_DV)
unnamed: R208.2, U12.33 (RX_CTL/CLK125_EN)
unnamed: R209.1, R219.1, U2.N10 (MII4_RXD0)
unnamed: R209.2, U12.32 (RXD0/MODE0)
unnamed: R210.2, U12.31 (RXD1/MODE1)
unnamed: R211.2, U12.28 (RXD2/MODE2)
unnamed: R212.2, U12.27 (RXD3/MODE3)
unnamed: R213.1, U2.N9 (MII4_TX_CLK)
unnamed: R213.2, U12.24 (TXC)
unnamed: R214.1, U2.P9 (MII4_TX_EN)
unnamed: R214.2, U12.25 (TX_CTL)
unnamed: R215.1, U2.P7 (MII4_TXD0)
unnamed: R215.2, U12.19 (TXD0)
unnamed: R216.1, U2.N7 (MII4_TXD1)
unnamed: R216.2, U12.20 (TXD1)
unnamed: R217.1, U2.P8 (MII4_TXD2)
unnamed: R217.2, U12.21 (TXD2)
unnamed: R218.1, U2.N8 (MII4_TXD3)
unnamed: R218.2, U12.22 (TXD3)
unnamed: R230.1, U14.16 (SW0)
unnamed: R239.1, U14.17 (SW1)
unnamed: R248.1, U14.18 (SW2)
unnamed: R257.1, U14.19 (SW3)
unnamed: R266.1, U14.20 (SW4)
unnamed: R269.1, U14.22 (RT)
unnamed: R277.1, U15.16 (SW0)
unnamed: R286.1, U15.17 (SW1)
unnamed: R289.1, U15.22 (RT)
unnamed: R293.1, U16.4 (GPIO2)
unnamed: R294.1, U16.5 (GPIO3)
unnamed: R295.1, U16.7 (GPIO5)
unnamed: R297.1, U16.8 (GPIO6)
unnamed: R298.1, U16.9 (GPIO7)
unnamed: R299.1, U16.11 (GPIO8)
unnamed: R300.1, U16.12 (GPIO9)
unnamed: R301.1, U16.14 (GPIO11)
unnamed: R302.1, U16.16 (GPIO13)
unnamed: R303.1, U16.18 (GPIO15)
unnamed: R304.1, U16.28 (GPIO17)
unnamed: R306.1, U16.30 (GPIO19)
unnamed: R307.1, U16.32 (GPIO21)
unnamed: R308.2, U16.21 (XOUT)
unnamed: R309.1, U16.35 (GPIO23)
unnamed: R310.1, U16.37 (GPIO25)
unnamed: R311.1, U16.38 (GPIO26_ADC0)
unnamed: R312.2, SW2.2
unnamed: R313.1, U16.41 (GPIO29_ADC3)
unnamed: R317.2, R318.1, U18.6 (FB)
unnamed: U1.N3 (TDO), U2.M2 (TDI)
unnamed: U1.N4 (PTP_CLK), U2.N4 (PTP_CLK)
PoDL_AUTO: R311.2, U14.13 (AUTO), U15.13 (AUTO)
REG0_LSNS0: C214.2, Q31.5 (D), R232.1, R241.1, R250.1, R259.1, R268.1, R270.2, U14.26 (LSNS0), U14.28 (LSNS1/LSNS2), U14.31 (LSNS3/LSNS4)
REG1_LSNS0: C225.2, Q44.5 (D), R279.1, R288.1, R290.2, U15.26 (LSNS0), U15.28 (LSNS1/LSNS2), U15.31 (LSNS3/LSNS4)
SPI0_MISO: U1.P4 (SDO), U2.P4 (SDO), U14.10 (SDO), U15.10 (SDO), U16.6 (GPIO4)
SPI0_MOSI: R294.2, U1.N5 (SDI), U2.N5 (SDI), U14.9 (SDI), U15.9 (SDI)
SPI0_SCK: R293.2, U1.P5 (SCK), U2.P5 (SCK), U14.11 (SCK), U15.11 (SCK)
SPI0_SS0: R295.2, U1.N6 (SS_N)
SPI0_SS1: R297.2, U2.N6 (SS_N)
SPI0_SS2: R298.2, U14.12 (nCS)
SPI0_SS3: R299.2, U15.12 (nCS)

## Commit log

2023-04-06 Create LICENSE
2023-04-06 Adding README in doc
2023-04-10 Initial Schematic Commit
2023-04-10 Update Schematic Name
2023-04-10 Removing Deleted Sheets
2023-04-10 Renaming Sheets
2023-04-10 Minor corrections
2023-04-10 Assigning Footprints
2023-04-10 Pinout Correction for LTC4296 and cleanup
2023-04-10 New Schematic
2023-04-10 New Schematic PDF
2023-04-10 Fixing termination for T1L PHYs
2023-04-11 Update Schematic PDF
2023-04-12 Correcting SCCP spelling
2023-04-12 Restructuring Repo
2023-04-17 Initial Placement and Hierarchical Schematic
2023-04-17 Removing unused files
2023-04-17 Updating Label Orientation
2023-04-18 Smaller Cicruit Corrections
2023-04-18 Updating Schematic PDF and Placement Images
2023-04-18 Adding Overview Schema
